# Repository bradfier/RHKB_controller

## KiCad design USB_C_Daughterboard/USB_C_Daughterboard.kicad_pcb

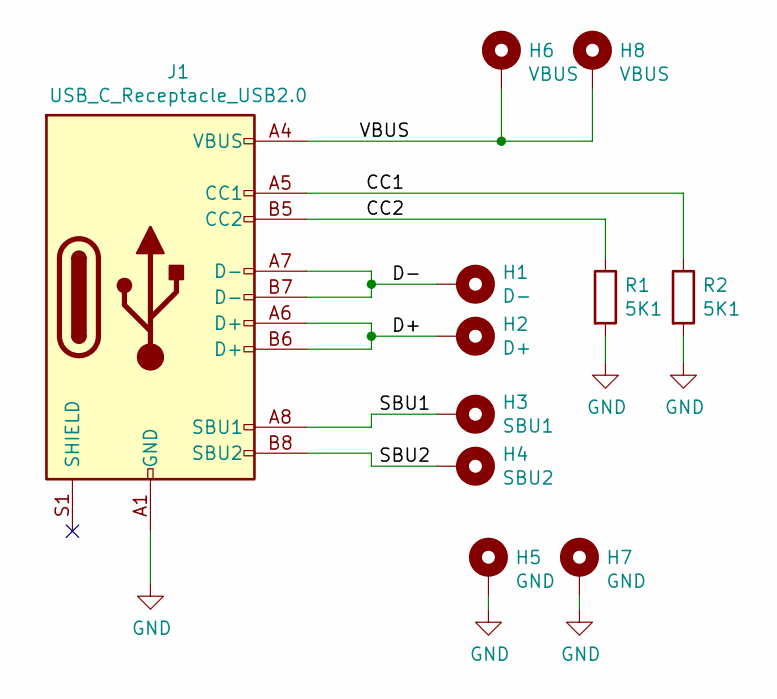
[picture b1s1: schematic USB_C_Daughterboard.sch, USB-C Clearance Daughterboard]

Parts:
H1: D-; TestPoint_THTPad_D1.5mm_Drill0.7mm
H2: D+; TestPoint_THTPad_D1.5mm_Drill0.7mm
H3: SBU1; TestPoint_THTPad_D1.5mm_Drill0.7mm
H4: SBU2; TestPoint_THTPad_D1.5mm_Drill0.7mm
H5, H7: GND; TestPoint_THTPad_D1.5mm_Drill0.7mm
H6, H8: VBUS; TestPoint_THTPad_D1.5mm_Drill0.7mm
J1: USB_C_Receptacle_USB2.0; USB_C_Receptacle_JAE_DX07S016JA1
R1, R2: 5K1; R_0603_1608Metric

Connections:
/CC1: J1.A5 (CC1), R2.1
/CC2: J1.B5 (CC2), R1.1
/D+: H2.1, J1.A6 (D+), J1.B6 (D+)
/D-: H1.1, J1.A7 (D-), J1.B7 (D-)
/SBU1: H3.1, J1.A8 (SBU1)
/SBU2: H4.1, J1.B8 (SBU2)
/VBUS: H6.1, H8.1, J1.A4 (VBUS), J1.A9 (VBUS), J1.B4 (VBUS), J1.B9 (VBUS)
GND: H5.1, H7.1, J1.A1 (GND), J1.A12 (GND), J1.B1 (GND), J1.B12 (GND), R1.2, R2.2

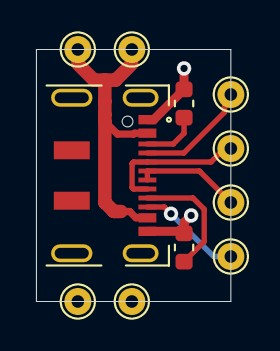
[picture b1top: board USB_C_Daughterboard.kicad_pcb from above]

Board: 2 copper layers, 10.8 x 14.0 mm, 11 parts (0 on the bottom side), 8 nets.

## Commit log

2020-06-12 Initial commit, with USB-C daughterboard
2020-06-12 Add TPS63000 SMPS block
2020-06-12 Rename daughterboard nets for better PCBnew labeling
2020-06-13 Add HHKB connectors and battery management modules
